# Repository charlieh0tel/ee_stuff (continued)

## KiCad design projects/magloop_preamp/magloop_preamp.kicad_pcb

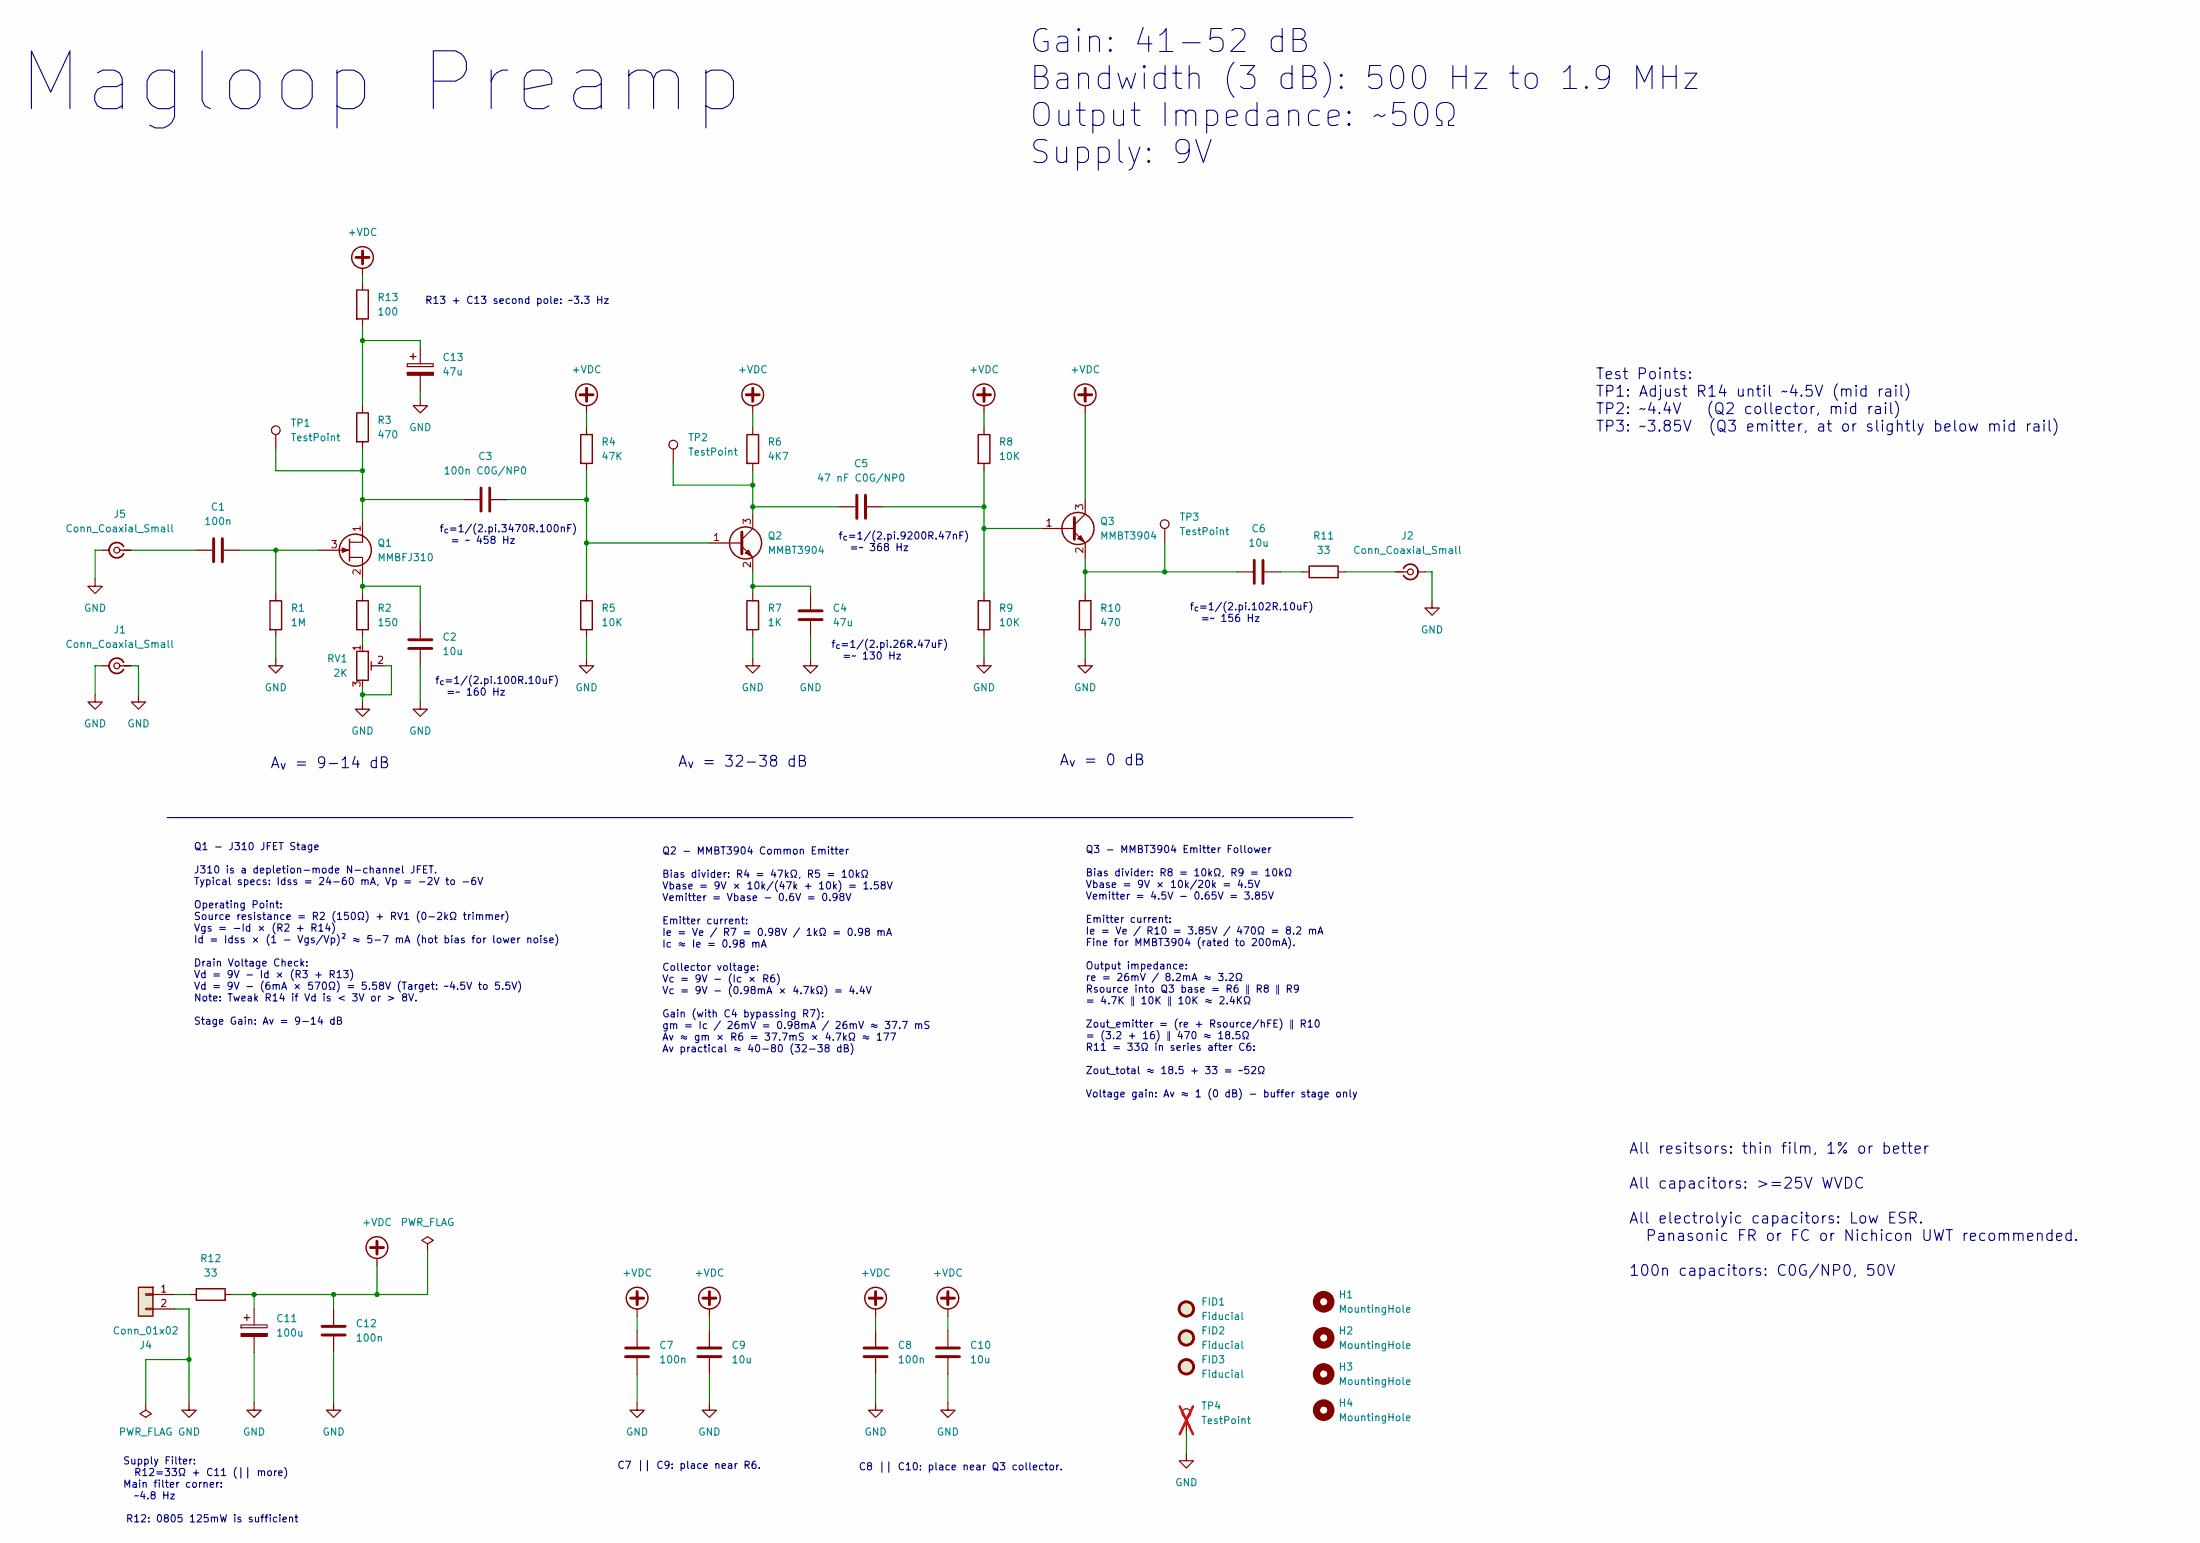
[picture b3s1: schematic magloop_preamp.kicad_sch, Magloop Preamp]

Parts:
C1, C7, C8, C12: 100n; C_0603_1608Metric
C2, C6, C9, C10: 10u; C_1206_3216Metric
C3: 100n C0G/NP0; C_1206_3216Metric
C4: 47u; C_1210_3225Metric
C5: 47 nF C0G/NP0; C_1206_3216Metric
C11: 100u; CP_EIA-7343-31_Kemet-D
C13: 47u; CP_EIA-6032-28_Kemet-C
FID1, FID2, FID3: Fiducial; Fiducial_0.5mm_Mask1.5mm
H1, H2, H3, H4: MountingHole; MountingHole_3.2mm_M3
J1, J2, J5: Conn_Coaxial_Small; SMA_Amphenol_901-144_Vertical
J4: Conn_01x02; Molex_KK-254_AE-6410-02A_1x02_P2.54mm_Vertical
Q1: MMBFJ310; TSOT-23
Q2, Q3: MMBT3904; TSOT-23
R1: 1M; R_0603_1608Metric
R2: 150; R_0603_1608Metric
R3, R10: 470; R_0603_1608Metric
R4: 47K; R_0603_1608Metric
R5, R8, R9: 10K; R_0603_1608Metric
R6: 4K7; R_0603_1608Metric
R7: 1K; R_0603_1608Metric
R11, R12: 33; R_0805_2012Metric
R13: 100; R_0603_1608Metric
RV1: 2K; Potentiometer_Bourns_3314G_Vertical
TP1, TP2, TP3: TestPoint; TestPoint_Pad_D1.0mm
TP4: TestPoint; TestPoint_Loop_D2.50mm_Drill1.0mm; not fitted

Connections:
+VDC: C7.1, C8.1, C9.1, C10.1, C11.1, C12.1, Q3.3 (C), R4.1, R6.1, R8.1, R12.2, R13.1
GND: C2.2, C4.2, C7.2, C8.2, C9.2, C10.2, C11.2, C12.2, C13.2, J1.1 (In), J1.2 (Ext), J2.2 (Ext), J4.2, J5.2 (Ext), R1.2, R5.2, R7.2, R9.2, R10.2, RV1.2, RV1.3, TP4.1
unnamed: C6.2, R11.1
unnamed: C13.1, R3.1, R13.2
unnamed: J2.1 (In), R11.2
unnamed: J4.1, R12.1
unnamed: C1.1, J5.1 (In)
unnamed: C3.1, Q1.1 (D), R3.2, TP1.1
unnamed: C1.2, Q1.3 (G), R1.1
unnamed: C2.1, Q1.2 (S), R2.1
unnamed: C3.2, Q2.1 (B), R4.2, R5.1
unnamed: C5.1, Q2.3 (C), R6.2, TP2.1
unnamed: C4.1, Q2.2 (E), R7.1
unnamed: C5.2, Q3.1 (B), R8.2, R9.1
unnamed: C6.1, Q3.2 (E), R10.1, TP3.1
unnamed: R2.2, RV1.1

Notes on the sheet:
Q2 - MMBT3904 Common Emitter Bias divider: R4 = 47kΩ, R5 = 10kΩ Vbase = 9V × 10k/(47k + 10k) = 1.58V Vemitter = Vbase - 0.6V = 0.98V Emitter current: Ie = Ve / R7 = 0.98V / 1kΩ = 0.98 mA Ic ≈ Ie = 0.98 mA Collector voltage: Vc = 9V - (Ic × R6) Vc = 9V - (0.98mA × 4.7kΩ) = 4.4V Gain (with C4 bypassi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
f_{c}=1/(2.pi.100R.10uF) =~ 160 Hz
f_{c}=1/(2.pi.3470R.100nF) = ~ 458 Hz
Magloop Preamp
A_{v} = 9-14 dB
Test Points: TP1: Adjust R14 until ~4.5V (mid rail) TP2: ~4.4V (Q2 collector, mid rail) TP3: ~3.85V (Q3 emitter, at or slightly below mid rail)
R13 + C13 second pole: ~3.3 Hz
f_{c}=1/(2.pi.26R.47uF) =~ 130 Hz
C7 || C9: place near R6.
A_{v} = 0 dB
Supply Filter: R12=33Ω + C11 (|| more) Main filter corner: ~4.8 Hz
Q1 - J310 JFET Stage J310 is a depletion-mode N-channel JFET. Typical specs: Idss = 24-60 mA, Vp = -2V to -6V Operating Point: Source resistance = R2 (150Ω) + RV1 (0-2kΩ trimmer) Vgs = -Id × (R2 + R14) Id = Idss × (1 - Vgs/Vp)² ≈ 5-7 mA (hot bias for lower noise) Drain Voltage Check: Vd = 9V - Id ×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
f_{c}=1/(2.pi.102R.10uF) =~ 156 Hz
A_{v} = 32-38 dB
All resitsors: thin film, 1% or better All capacitors: >=25V WVDC All electrolyic capacitors: Low ESR. Panasonic FR or FC or Nichicon UWT recommended. 100n capacitors: C0G/NP0, 50V
Gain: 41-52 dB Bandwidth (3 dB): 500 Hz to 1.9 MHz Output Impedance: ~50Ω Supply: 9V
Q3 - MMBT3904 Emitter Follower Bias divider: R8 = 10kΩ, R9 = 10kΩ Vbase = 9V × 10k/20k = 4.5V Vemitter = 4.5V - 0.65V = 3.85V Emitter current: Ie = Ve / R10 = 3.85V / 470Ω = 8.2 mA Fine for MMBT3904 (rated to 200mA). Output impedance: re = 26mV / 8.2mA ≈ 3.2Ω Rsource into Q3 base = R6 ‖ R8 ‖ R9 = 4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
f_{c}=1/(2.pi.9200R.47nF) =~ 368 Hz
C8 || C10: place near Q3 collector.
R12: 0805 125mW is sufficient

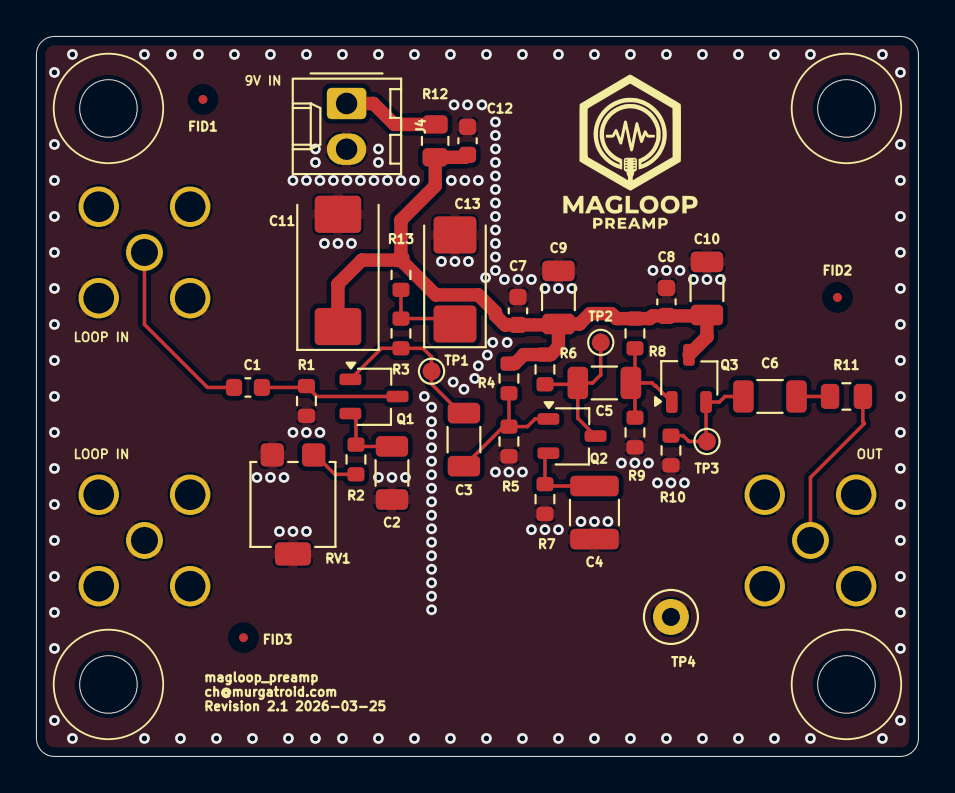
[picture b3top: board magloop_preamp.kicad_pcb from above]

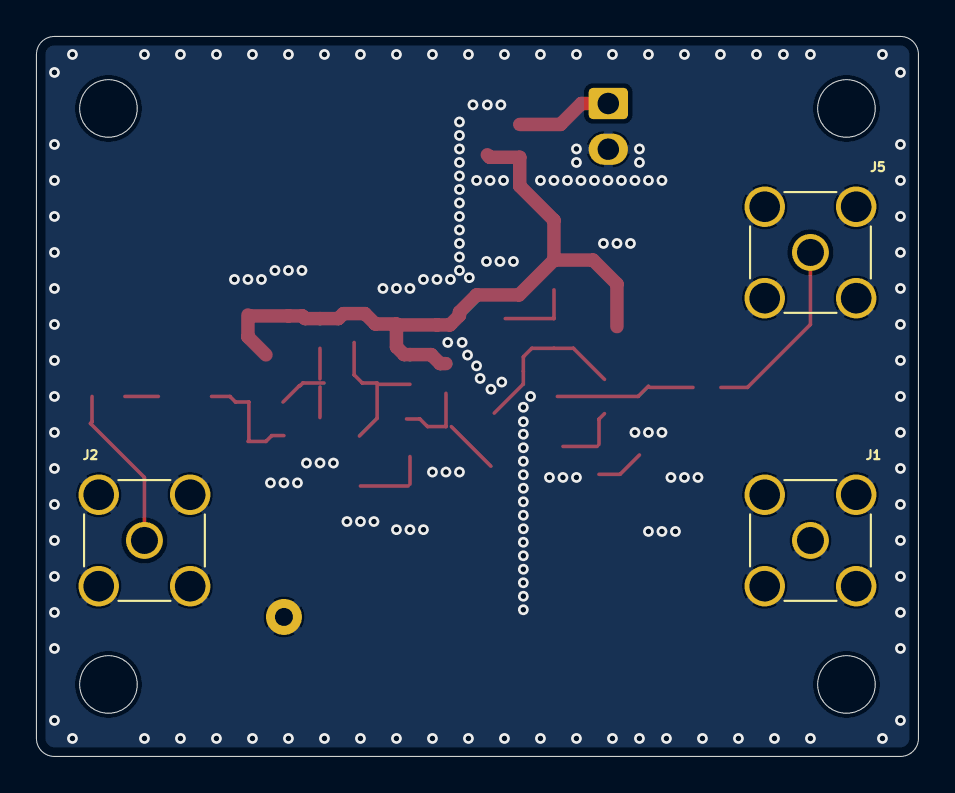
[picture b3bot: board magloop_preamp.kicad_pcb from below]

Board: 2 copper layers, 49.0 x 40.0 mm, 45 parts (3 on the bottom side), 16 nets.

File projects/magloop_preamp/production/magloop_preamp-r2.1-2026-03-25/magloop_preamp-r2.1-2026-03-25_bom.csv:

Designator,Footprint,Quantity,Value,LCSC Part #
"C1, C12, C7, C8",0603,4,100n,C14663
"C10, C2, C6, C9",1206,4,10u,C13585
C11,CP_EIA-7343-31_Kemet-D,1,100u,C7224
C13,CP_EIA-6032-28_Kemet-C,1,47u,C145123
C3,1206,1,100n C0G/NP0,C97946
C4,1210,1,47u,C90142
C5,1206,1,47 nF C0G/NP0,C21812
"J1, J2, J5",SMA_Amphenol_901-144_Vertical,3,Conn_Coaxial_Small,C5250058
Q1,TSOT-23,1,MMBFJ310,C33416
"Q2, Q3",TSOT-23,2,MMBT3904,C49435601
R1,0603,1,1M,C4250208
"R10, R3",0603,2,470,C705779
"R11, R12",0805,2,33,C218521
R13,0603,1,100,C122970
R2,0603,1,150,C860127
R4,0603,1,47K,C326725
"R5, R8, R9",0603,3,10K,C95204
R6,0603,1,4K7,C513565
R7,0603,1,1K,C110776
RV1,Potentiometer_Bourns_3314G_Vertical,1,2K,C711704
"TP1, TP2, TP3",TestPoint_Pad_D1.0mm,3,TestPoint,

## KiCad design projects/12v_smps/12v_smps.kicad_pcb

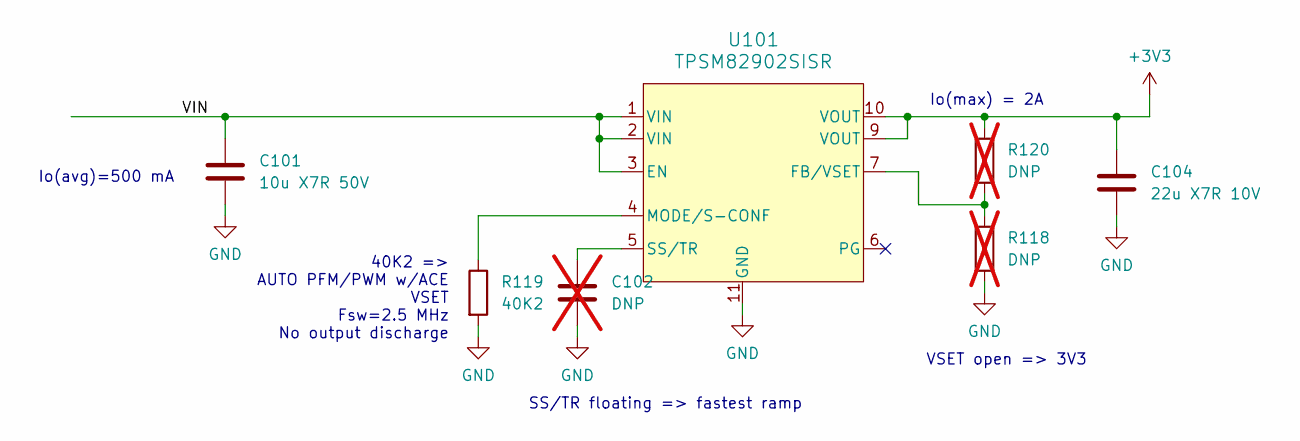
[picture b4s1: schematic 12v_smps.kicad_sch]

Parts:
C101: 10u X7R 50V; C_1206_3216Metric
C102: DNP; C_0402_1005Metric; not fitted
C104: 22u X7R 10V; C_1206_3216Metric
R118, R120: DNP; R_0402_1005Metric; not fitted
R119: 40K2; R_0402_1005Metric
U101: TPSM82902SISR; uSIP11_SIS_TEX

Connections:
+3V3: C104.1, R120.1, U101.9 (VOUT), U101.10 (VOUT)
/VIN: C101.1, U101.1 (VIN), U101.2 (VIN), U101.3 (EN)
GND: C101.2, C102.2, C104.2, R118.2, R119.2, U101.11 (GND)
unnamed: R118.1, R120.2, U101.7 (FB/VSET)
unnamed: R119.1, U101.4 (MODE/S-CONF)
unnamed: C102.1, U101.5 (SS/TR)

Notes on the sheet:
Io(max) = 2A
40K2 => AUTO PFM/PWM w/ACE VSET Fsw=2.5 MHz No output discharge
Io(avg)=500 mA
VSET open => 3V3
SS/TR floating => fastest ramp

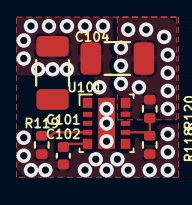
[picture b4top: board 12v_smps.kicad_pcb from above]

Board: 6 copper layers, 7 parts (0 on the bottom side), 6 nets.

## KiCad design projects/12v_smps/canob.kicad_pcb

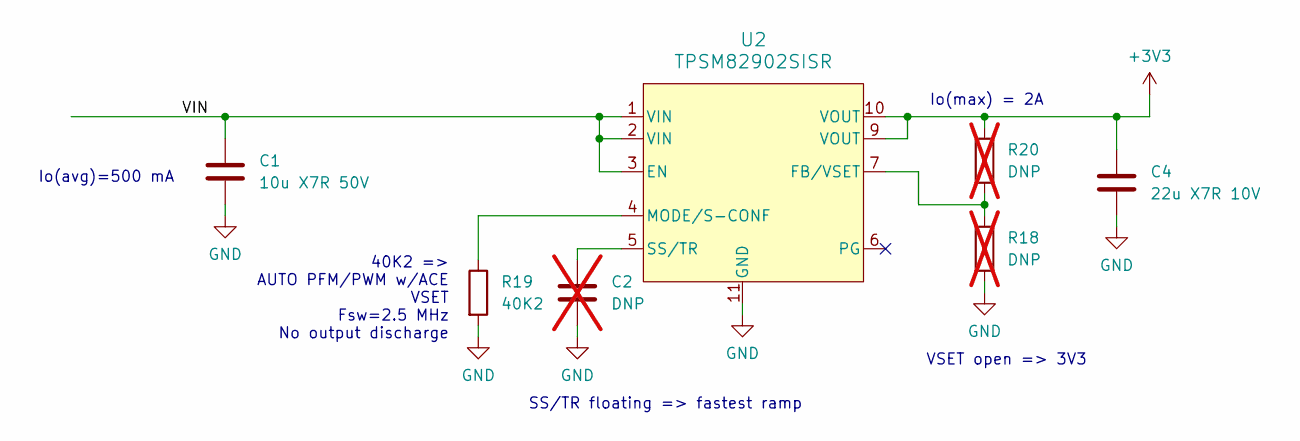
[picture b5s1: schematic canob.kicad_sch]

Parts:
C1: 10u X7R 50V; C_1206_3216Metric
C2: DNP; C_0402_1005Metric; not fitted
C4: 22u X7R 10V; C_1206_3216Metric
R18, R20: DNP; R_0402_1005Metric; not fitted
R19: 40K2; R_0402_1005Metric
U2: TPSM82902SISR; uSIP11_SIS_TEX

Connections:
+3V3: C4.1, R20.1, U2.9 (VOUT), U2.10 (VOUT)
/VIN: C1.1, U2.1 (VIN), U2.2 (VIN), U2.3 (EN)
GND: C1.2, C2.2, C4.2, R18.2, R19.2, U2.11 (GND)
unnamed: R18.1, R20.2, U2.7 (FB/VSET)
unnamed: R19.1, U2.4 (MODE/S-CONF)
unnamed: C2.1, U2.5 (SS/TR)

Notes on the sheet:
VSET open => 3V3
40K2 => AUTO PFM/PWM w/ACE VSET Fsw=2.5 MHz No output discharge
Io(max) = 2A
Io(avg)=500 mA
SS/TR floating => fastest ramp

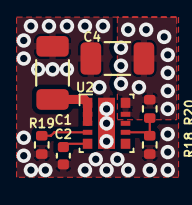
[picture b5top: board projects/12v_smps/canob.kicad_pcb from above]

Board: 6 copper layers, 7 parts (0 on the bottom side), 6 nets.

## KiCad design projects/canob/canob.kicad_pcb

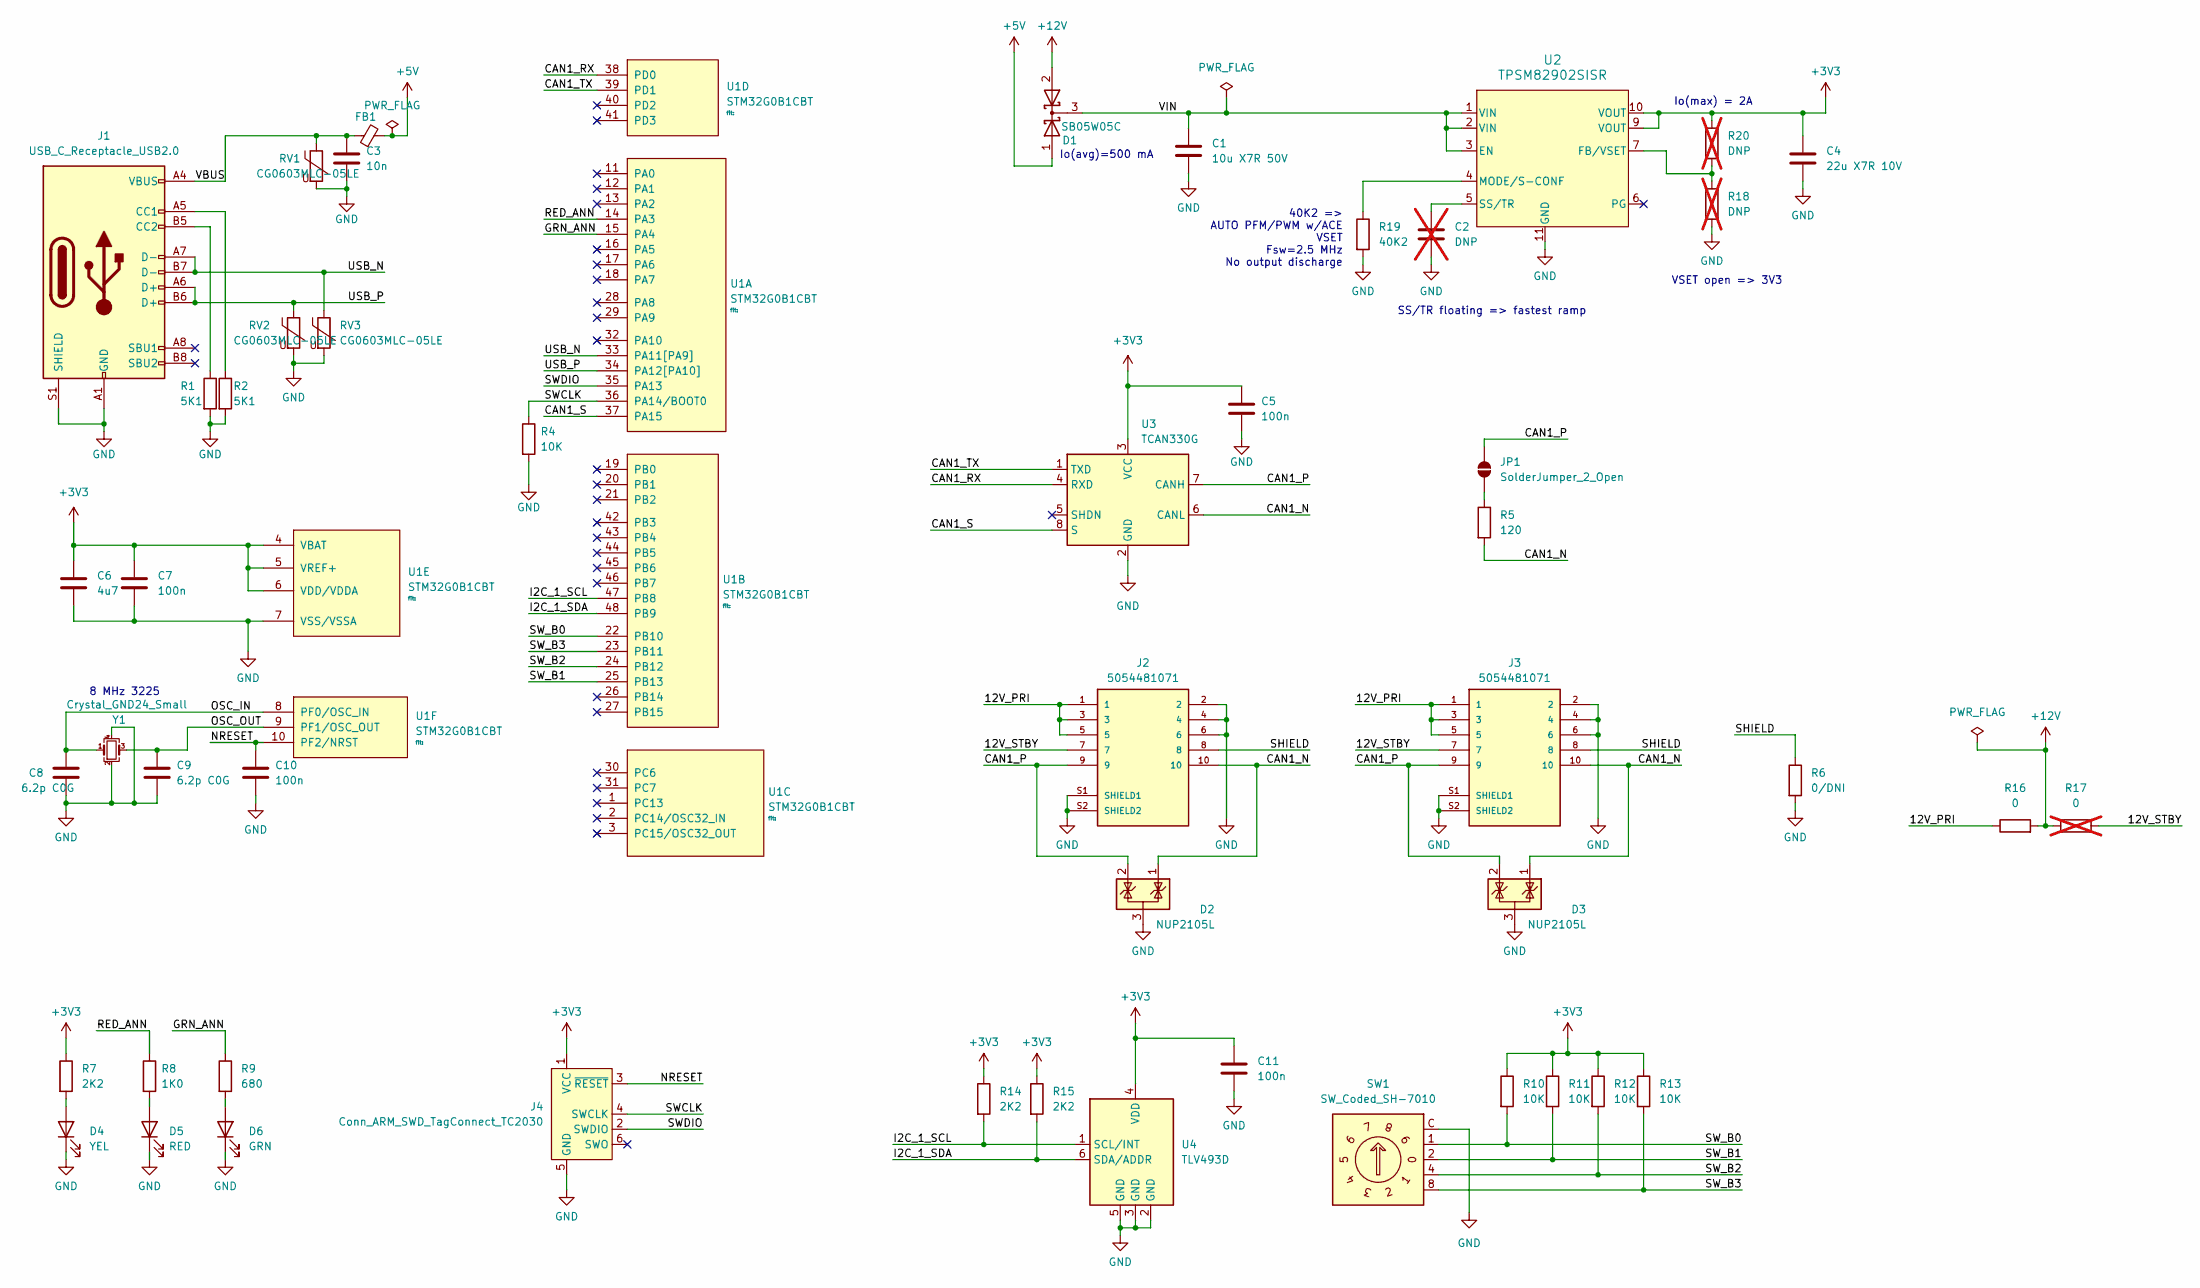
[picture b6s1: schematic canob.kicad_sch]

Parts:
C1: 10u X7R 50V; C_1206_3216Metric
C2: DNP; C_0402_1005Metric; not fitted
C3: 10n; C_0603_1608Metric
C4: 22u X7R 10V; C_1206_3216Metric
C5, C10, C11: 100n; C_0402_1005Metric
C6: 4u7; C_0603_1608Metric
C7: 100n; C_0603_1608Metric
C8, C9: 6.2p C0G; C_0402_1005Metric
D1: SB05W05C; SOT-23-3
D2, D3: NUP2105L; SOT-23; LCSC C284104
D4: YEL; LED_0402_1005Metric; MPN 150060YS75000
D5: RED; LED_0402_1005Metric; MPN 150060RS75000
D6: GRN; LED_0402_1005Metric; MPN 150060GS75000
FB1: FerriteBead_Small; D_0603_1608Metric_Pad1.05x0.95mm_HandSolder; LCSC C62708
J1: USB_C_Receptacle_USB2.0; USB_C_Receptacle_HCTL_HC-TYPE-C-16P-01A; LCSC C2997435
J2, J3: 5054481071; MOLEX_5054481071; PARTREV B; LCSC C17610436
J4: Conn_ARM_SWD_TagConnect_TC2030; Tag-Connect_TC2030-IDC-NL_2x03_P1.27mm_Vertical
JP1: SolderJumper_2_Open; SolderJumper-2_P1.3mm_Open_TrianglePad1.0x1.5mm
R1, R2: 5K1; R_0402_1005Metric
R4, R10, R11, R12, R13: 10K; R_0402_1005Metric
R5: 120; R_1206_3216Metric
R6: 0/DNI; R_0402_1005Metric
R7, R14, R15: 2K2; R_0402_1005Metric
R8: 1K0; R_0402_1005Metric
R9: 680; R_0402_1005Metric
R16: 0; R_0402_1005Metric
R17: 0; R_0402_1005Metric; not fitted
R18, R20: DNP; R_0402_1005Metric; not fitted
R19: 40K2; R_0402_1005Metric
RV1, RV2, RV3: CG0603MLC-05LE; R_0603_1608Metric; LCSC C2655331
SW1: SW_Coded_SH-7010; SKAR-10S
U1: STM32G0B1CBT; LQFP-48_7x7mm_P0.5mm; MPN STM32G0B1CBT
U2: TPSM82902SISR; uSIP11_SIS_TEX
U3: TCAN330G; TSOT-23-8
U4: TLV493D; SOT-23-6
Y1: Crystal_GND24_Small; Crystal_SMD_3225-4Pin_3.2x2.5mm; LCSC C518135

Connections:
+3V3: C4.1, C5.1, C6.1, C7.1, C11.1, J4.1 (VCC), R7.1, R10.1, R11.1, R12.1, R13.1, R14.1, R15.1, R20.1, U1.4 (VBAT), U1.5 (VREF+), U1.6 (VDD/VDDA), U2.9 (VOUT), U2.10 (VOUT), U3.3 (VCC), U4.4 (VDD)
+5V: D1.1 (A), FB1.2
+12V: D1.2 (A), R16.2, R17.1
/12V_PRI: J2.1, J2.3, J2.5, J3.1, J3.3, J3.5, R16.1
/12V_STBY: J2.7, J3.7, R17.2
/CAN1_N: D2.1 (K), D3.1 (K), J2.10, J3.10, R5.2, U3.6 (CANL)
/CAN1_P: D2.2 (K), D3.2 (K), J2.9, J3.9, JP1.2 (B), U3.7 (CANH)
/CAN1_RX: U1.38 (PD0), U3.4 (RXD)
/CAN1_S: U1.37 (PA15), U3.8 (S)
/CAN1_TX: U1.39 (PD1), U3.1 (TXD)
/GRN_ANN: R9.1, U1.15 (PA4)
/I2C_1_SCL: R14.2, U1.47 (PB8), U4.1 (SCL/INT)
/I2C_1_SDA: R15.2, U1.48 (PB9), U4.6 (SDA/ADDR)
/NRESET: C10.1, J4.3 (~RESET), U1.10 (PF2/NRST)
/OSC_IN: C8.1, U1.8 (PF0/OSC_IN), Y1.1
/OSC_OUT: C9.1, U1.9 (PF1/OSC_OUT), Y1.3
/RED_ANN: R8.1, U1.14 (PA3)
/SHIELD: J2.8, J3.8, R6.1
/SWCLK: J4.4 (SWCLK), R4.1, U1.36 (PA14/BOOT0)
/SWDIO: J4.2 (SWDIO), U1.35 (PA13)
/SW_B0: R10.2, SW1.1, U1.22 (PB10)
/SW_B1: R11.2, SW1.2, U1.25 (PB13)
/SW_B2: R12.2, SW1.4, U1.24 (PB12)
/SW_B3: R13.2, SW1.8, U1.23 (PB11)
/USB_N: J1.A7 (D-), J1.B7 (D-), RV3.1, U1.33 (PA11[PA9])
/USB_P: J1.A6 (D+), J1.B6 (D+), RV2.1, U1.34 (PA12[PA10])
/VBUS: C3.1, FB1.1, J1.A4 (VBUS), J1.A9 (VBUS), J1.B4 (VBUS), J1.B9 (VBUS), RV1.1
/VIN: C1.1, D1.3 (K), U2.1 (VIN), U2.2 (VIN), U2.3 (EN)
GND: C1.2, C2.2, C3.2, C4.2, C5.2, C6.2, C7.2, C8.2, C9.2, C10.2, C11.2, D2.3 (A), D3.3 (A), D4.1 (K), D5.1 (K), D6.1 (K), J1.A1 (GND), J1.A12 (GND), J1.B1 (GND), J1.B12 (GND), J1.S1 (SHIELD), J2.2, J2.4, J2.6, J2.S1 (SHIELD1), J2.S2 (SHIELD2), J3.2, J3.4, J3.6, J3.S1 (SHIELD1), J3.S2 (SHIELD2), J4.5 (GND), R1.2, R2.2, R4.2, R6.2, R18.2, R19.2, RV1.2, RV2.2, RV3.2, SW1.C, U1.7 (VSS/VSSA), U2.11 (GND), U3.2 (GND), U4.2 (GND), U4.3 (GND), U4.5 (GND), Y1.2, Y1.4
unnamed: D4.2 (A), R7.2
unnamed: D5.2 (A), R8.2
unnamed: D6.2 (A), R9.2
unnamed: J1.A5 (CC1), R2.1
unnamed: J1.B5 (CC2), R1.1
unnamed: JP1.1 (A), R5.1
unnamed: R18.1, R20.2, U2.7 (FB/VSET)
unnamed: R19.1, U2.4 (MODE/S-CONF)
unnamed: C2.1, U2.5 (SS/TR)

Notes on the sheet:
8 MHz 3225
Io(max) = 2A
40K2 => AUTO PFM/PWM w/ACE VSET Fsw=2.5 MHz No output discharge
Io(avg)=500 mA
VSET open => 3V3
SS/TR floating => fastest ramp

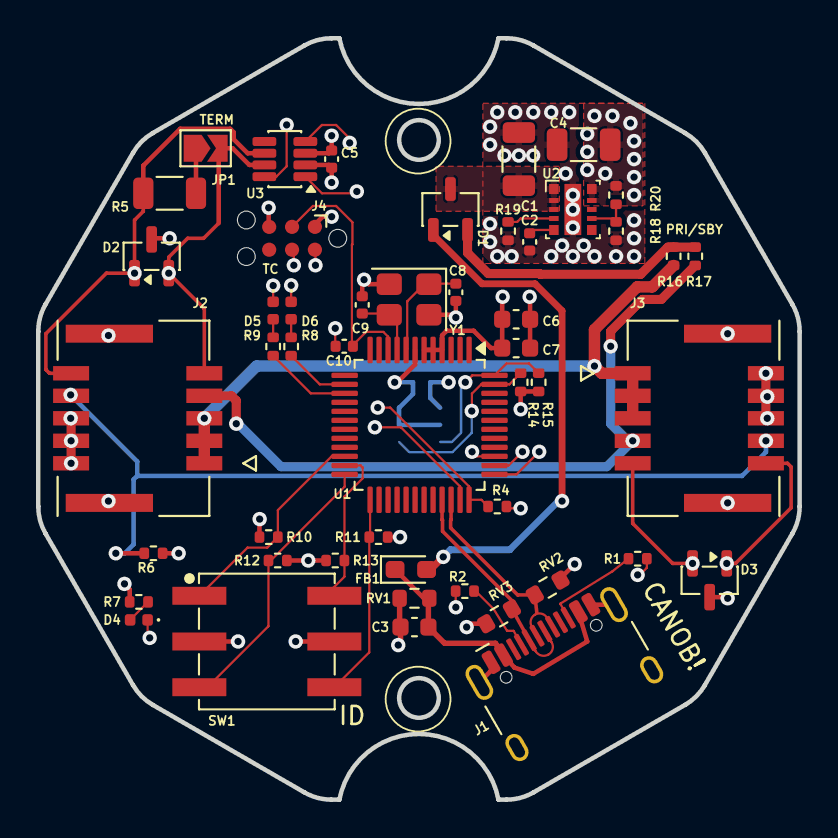
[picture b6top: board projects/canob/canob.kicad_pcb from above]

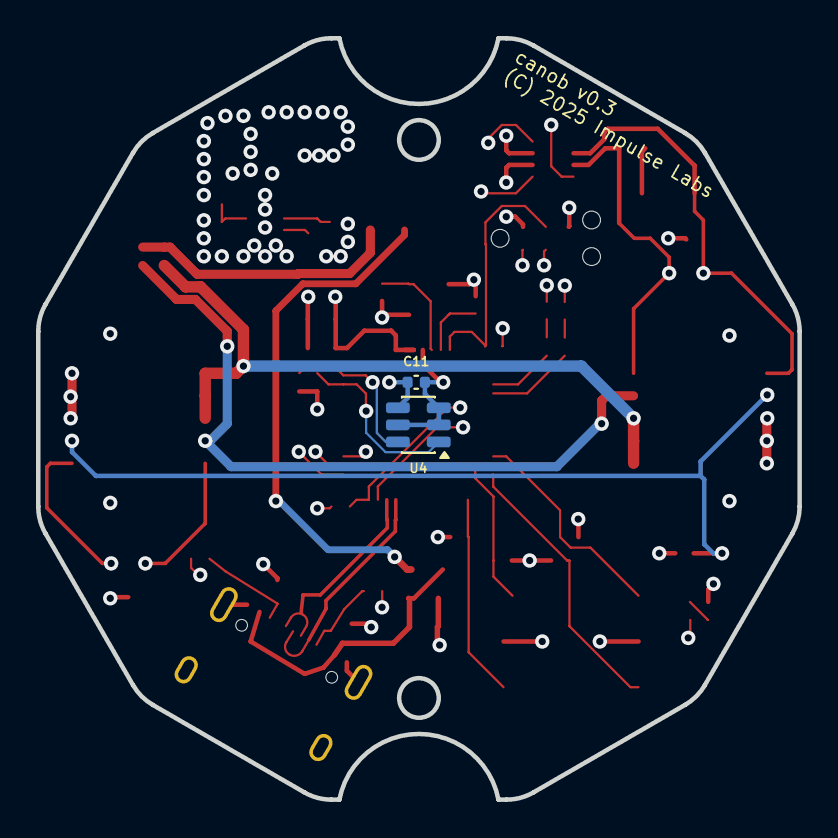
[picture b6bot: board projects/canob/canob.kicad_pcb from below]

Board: 6 copper layers, 42.3 x 42.3 mm, 51 parts (2 on the bottom side), 38 nets.

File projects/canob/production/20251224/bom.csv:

Designator,Footprint,Quantity,Value,LCSC Part #
C1,1206,1,10u X7R 50V,
C10,0402,1,100n,C14663
"C11, C5",0402,2,100n,
C3,0603,1,10n,C14663
C4,1206,1,22u X7R 10V,
C6,0603,1,4u7,
C7,0603,1,100n,C14663
C8,0402,1,6.2p C0G,
C9,0402,1,6.2p C0G,C14663
D1,SOT-23-3,1,SB05W05C,
"D2, D3",SOT-23,2,NUP2105L,C284104
D4,0402,1,YEL,C9900012286
D5,0402,1,RED,C3030991
D6,0402,1,GRN,C5252984
FB1,0603,1,FerriteBead_Small,C62708
J1,USB_C_Receptacle_HCTL_HC-TYPE-C-16P-01A,1,USB_C_Receptacle_USB2.0,C2997435
"J2, J3",MOLEX_5054481071,2,5054481071,C17610436
"R1, R2",0402,2,5K1,
"R10, R11, R12, R13, R4",0402,5,10K,
"R14, R7",0402,2,2K2,
R15,0402,1,2K2,C473612
R16,0402,1,0,
R19,0402,1,40K2,
R5,1206,1,120,
R6,0402,1,0/DNI,C473612
R8,0402,1,1K0,
R9,0402,1,680,
"RV1, RV2, RV3",0603,3,CG0603MLC-05LE,C2655331
SW1,Nidec_Copal_SH-7010A,1,SW_Coded_SH-7010,
U1,LQFP-48_7x7mm_P0.5mm,1,STM32G0B1CBT,STM32G0B1CBT
U2,uSIP11_SIS_TEX,1,TPSM82902SISR,
U3,TSOT-23-8,1,TCAN330G,
U4,SOT-23-6,1,TLV493D,
Y1,Crystal_SMD_3225-4Pin_3.2x2.5mm,1,Crystal_GND24_Small,C518135

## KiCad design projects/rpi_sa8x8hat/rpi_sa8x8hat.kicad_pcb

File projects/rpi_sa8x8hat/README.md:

# SA-8x8 Hat for Raspberry Pi #

WIP.

# Acknowledgments #

* rPi HAT template from https://github.com/devbisme/RPi_Hat_Template

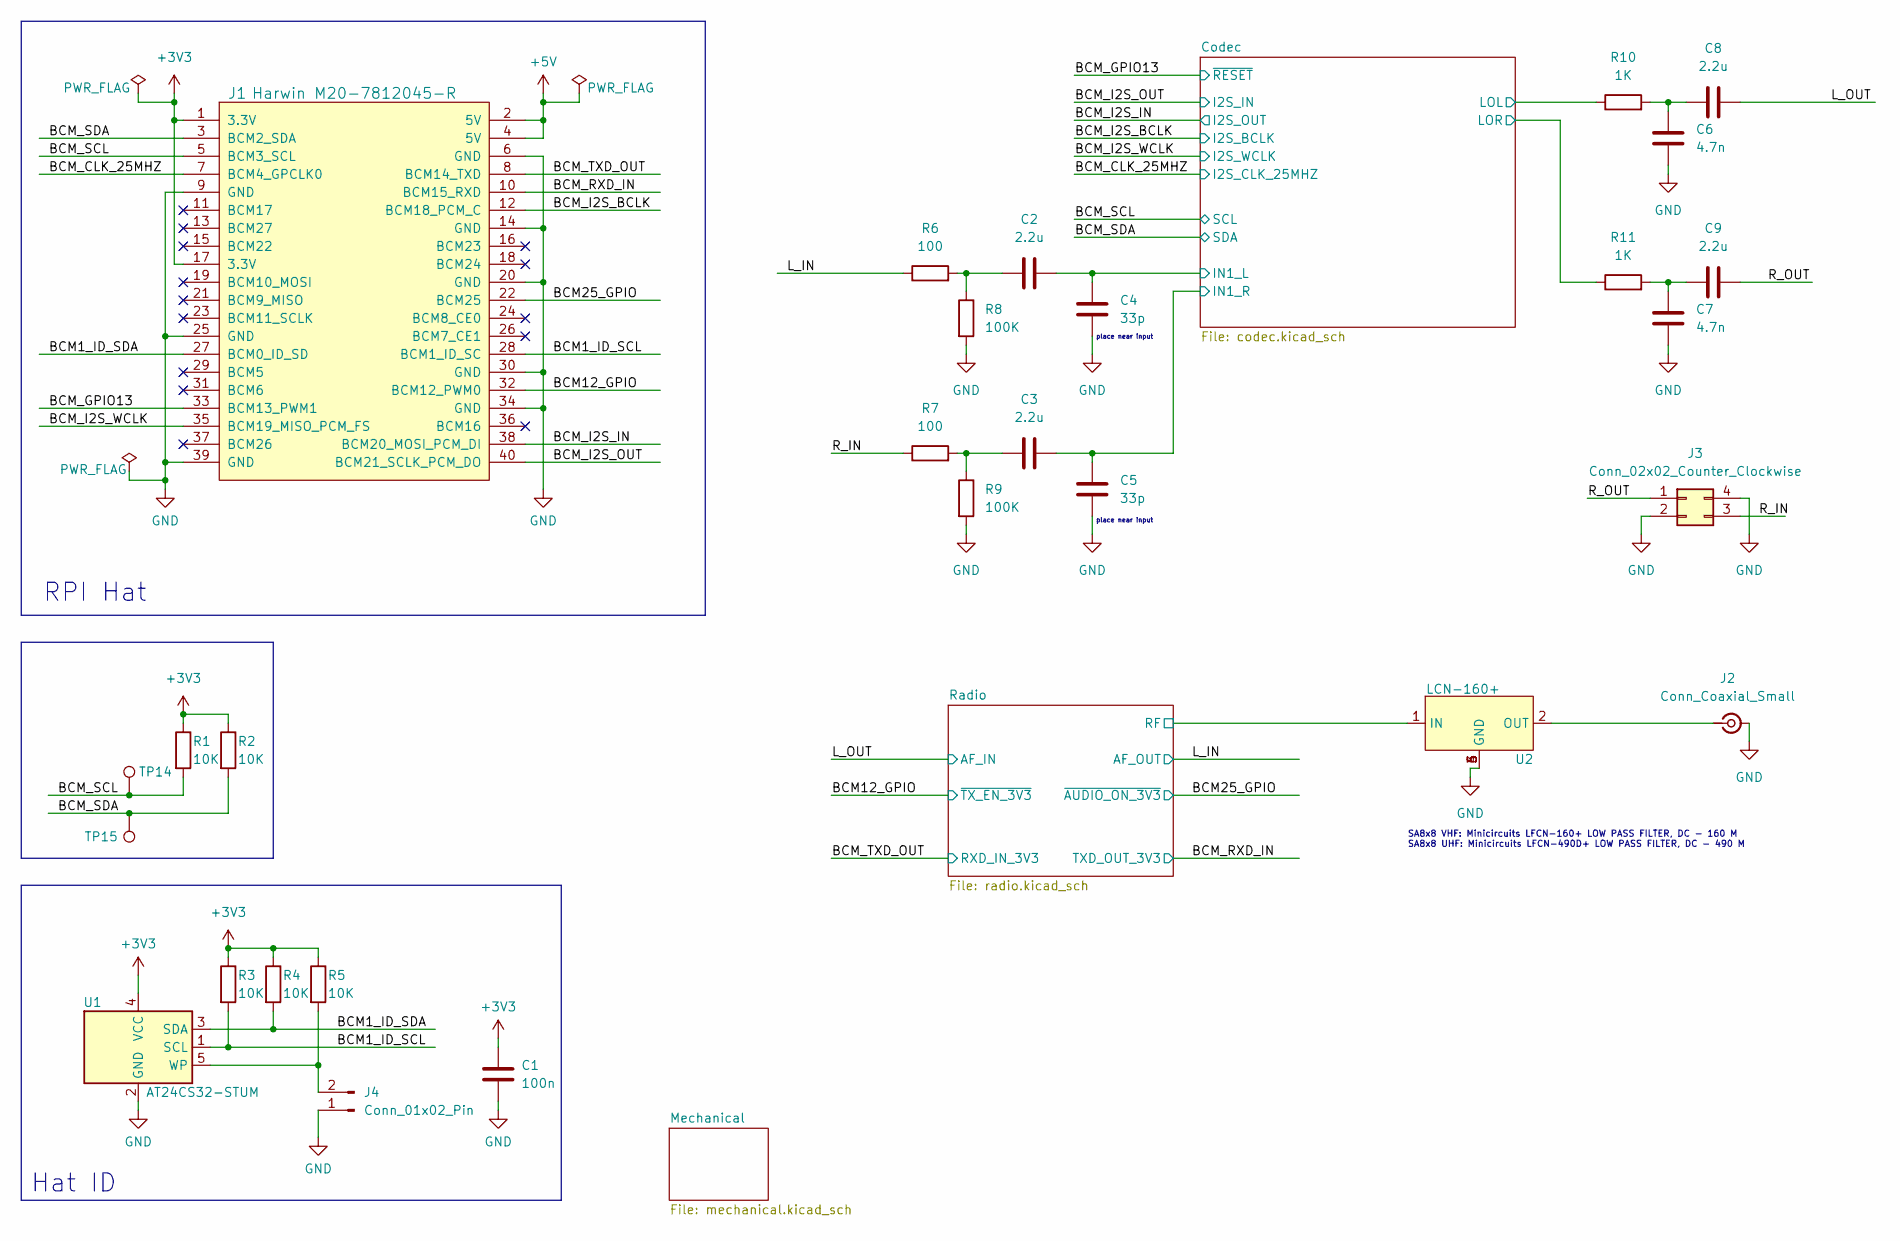
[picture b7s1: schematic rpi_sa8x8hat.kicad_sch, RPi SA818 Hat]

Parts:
C1: 100n; C_0402_1005Metric
C2, C3: 2.2u; C_0201_0603Metric
C4, C5: 33p; C_0402_1005Metric
C6, C7: 4.7n; C_0402_1005Metric
C8, C9: 2.2u; C_0402_1005Metric
J1: Harwin M20-7812045-R; MPN M20-7812045; LCSC C42411761
J2: Conn_Coaxial_Small; SMA_Amphenol_901-143_Horizontal
J3: Conn_02x02_Counter_Clockwise; Molex_Micro-Fit_3.0_43045-0412_2x02_P3.00mm_Vertical
J4: Conn_01x02_Pin; PinHeader_1x02_P2.00mm_Vertical_SMD_Pin1Left
R1, R2: 10K; R_0402_1005Metric
R3, R4, R5: 10K; R_0201_0603Metric
R6, R7: 100; R_0402_1005Metric
R8, R9: 100K; R_0402_1005Metric
R10, R11: 1K; R_0402_1005Metric
TP14, TP15: TestPoint; TestPoint_Pad_D1.0mm
U1: AT24CS32-STUM; SOT-23-5
U2: LCN-160+; LFCN

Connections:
+3V3: C1.1, J1.1 (3.3V), J1.17 (3.3V), R1.1, R2.1, R3.1, R4.1, R5.1, U1.4 (VCC); also elsewhere on the board
+5V: J1.2 (5V), J1.4 (5V); also elsewhere on the board
/BCM1_ID_SCL: J1.28 (BCM1_ID_SC), R3.2, U1.1 (SCL)
/BCM1_ID_SDA: J1.27 (BCM0_ID_SD), R4.2, U1.3 (SDA)
/BCM12_GPIO: J1.32 (BCM12_PWM0); also elsewhere on the board
/BCM25_GPIO: J1.22 (BCM25); also elsewhere on the board
/BCM_CLK_25MHZ: J1.7 (BCM4_GPCLK0); also elsewhere on the board
/BCM_GPIO13: J1.33 (BCM13_PWM1); also elsewhere on the board
/BCM_I2S_BCLK: J1.12 (BCM18_PCM_C); also elsewhere on the board
/BCM_I2S_IN: J1.38 (BCM20_MOSI_PCM_DI); also elsewhere on the board
/BCM_I2S_OUT: J1.40 (BCM21_SCLK_PCM_DO); also elsewhere on the board
/BCM_I2S_WCLK: J1.35 (BCM19_MISO_PCM_FS); also elsewhere on the board
/BCM_RXD_IN: J1.10 (BCM15_RXD); also elsewhere on the board
/BCM_SCL: J1.5 (BCM3_SCL), R1.2, TP14.1; also elsewhere on the board
/BCM_SDA: J1.3 (BCM2_SDA), R2.2, TP15.1; also elsewhere on the board
/BCM_TXD_OUT: J1.8 (BCM14_TXD); also elsewhere on the board
/Codec/IN1_L: C2.2, C4.1; also elsewhere on the board
/Codec/IN1_R: C3.2, C5.1; also elsewhere on the board
/Codec/LOL: R10.1; also elsewhere on the board
/Codec/LOR: R11.1; also elsewhere on the board
/L_IN: R6.1; also elsewhere on the board
/L_OUT: C8.2; also elsewhere on the board
/R_IN: J3.3, R7.1
/R_OUT: C9.2, J3.1
/Radio/RF: U2.1 (IN); also elsewhere on the board
GND: C1.2, C4.2, C5.2, C6.2, C7.2, J1.6 (GND), J1.9 (GND), J1.14 (GND), J1.20 (GND), J1.25 (GND), J1.30 (GND), J1.34 (GND), J1.39 (GND), J2.2 (Ext), J3.2, J3.4, J4.1, R8.2, R9.2, U1.2 (GND), U2.3 (GND), U2.4 (GND), U2.5 (GND), U2.6 (GND); also elsewhere on the board
unnamed: C2.1, R6.2, R8.1
unnamed: C3.1, R7.2, R9.1
unnamed: C6.1, C8.1, R10.2
unnamed: C7.1, C9.1, R11.2
unnamed: J2.1 (In), U2.2 (OUT)
unnamed: J4.2, R5.2, U1.5 (WP)

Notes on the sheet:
RPI Hat
SA8x8 VHF: Minicircuits LFCN-160+ LOW PASS FILTER, DC - 160 M SA8x8 UHF: Minicircuits LFCN-490D+ LOW PASS FILTER, DC - 490 M
Hat ID
place near input
